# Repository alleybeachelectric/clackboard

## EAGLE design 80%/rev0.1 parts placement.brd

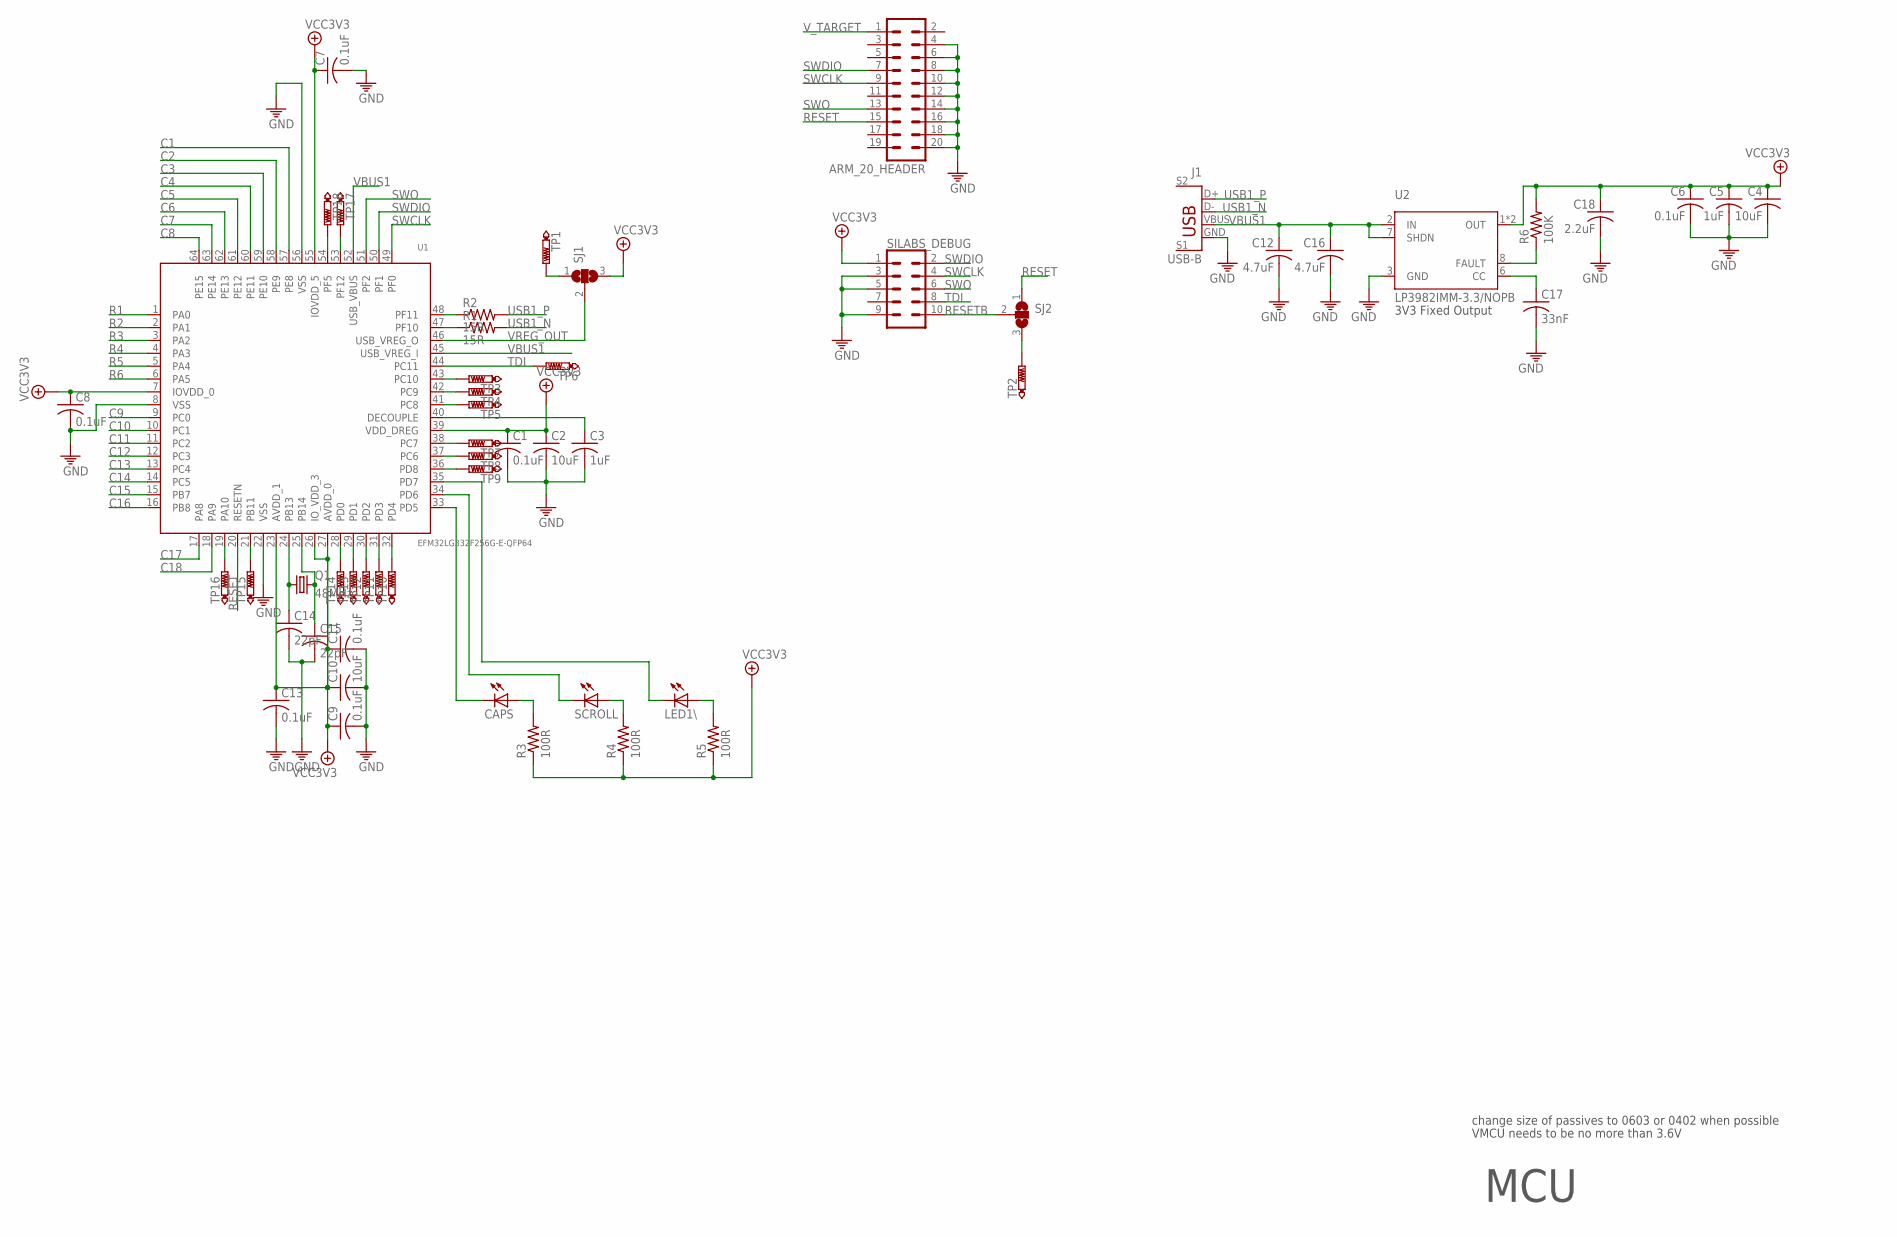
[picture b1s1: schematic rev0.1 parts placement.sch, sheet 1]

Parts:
ARM_20_HEADER: MA10-2
C1, C6, C7, C8, C9, C11, C13: 0.1uF; C0402
C2, C4, C10: 10uF; C0805
C3, C5: 1uF; C0402
C12, C16: 4.7uF; C0805
C14, C15: 22pF; C0402
C17: 33nF; C0402
C18: 2.2uF; C0805
CAPS: LEDCHIP-LED0805; CHIP-LED0805
J1: USB-B; USB-B-PTH
LED1\: LEDCHIP-LED0805; CHIP-LED0805
Q1: 48MHz; CTS406
R1, R2: 15R; R0402
R3, R4, R5: 100R; R0402
R6: 100K; R0402
SCROLL: LEDCHIP-LED0805; CHIP-LED0805
SILABS_DEBUG: CONN_05X2SHD_LOCK; 2X5-SHROUDED_LOCK
SJ1, SJ2: SJ2W; SJ_2
TP1, TP2: PTR1B2,54; B2,54
TP3, TP4, TP5, TP6, TP7, TP8, TP9, TP10, TP11, TP12, TP13, TP14, TP15, TP16, TP17, TP18: PTR1B1,27; B1,27
U1: EFM32LG332F256G-E-QFP64
U2: LP3982IMM-3.3/NOPB

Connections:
1_N: R1.1, U1.47 (PF10)
1_P: R2.1, U1.48 (PF11)
C1: U1.57 (PE8); also elsewhere on the board
C2: U1.58 (PE9); also elsewhere on the board
C3: U1.59 (PE10); also elsewhere on the board
C4: U1.60 (PE11); also elsewhere on the board
C5: U1.61 (PE12); also elsewhere on the board
C6: U1.62 (PE13); also elsewhere on the board
C7: U1.63 (PE14); also elsewhere on the board
C8: U1.64 (PE15); also elsewhere on the board
C9: U1.9 (PC0); also elsewhere on the board
C10: U1.10 (PC1); also elsewhere on the board
C11: U1.11 (PC2); also elsewhere on the board
C12: U1.12 (PC3); also elsewhere on the board
C13: U1.13 (PC4); also elsewhere on the board
C14: U1.14 (PC5); also elsewhere on the board
C15: U1.15 (PB7); also elsewhere on the board
C16: U1.16 (PB8); also elsewhere on the board
C17: U1.17 (PA8); also elsewhere on the board
C18: U1.18 (PA9); also elsewhere on the board
GND: ARM_20_HEADER.4, ARM_20_HEADER.6, ARM_20_HEADER.8, ARM_20_HEADER.10, ARM_20_HEADER.12, ARM_20_HEADER.14, ARM_20_HEADER.16, ARM_20_HEADER.18, ARM_20_HEADER.20, C1.2, C2.2, C3.2, C4.2, C5.2, C6.2, C7.2, C8.2, C9.2, C10.2, C11.2, C12.2, C13.2, C14.2, C15.2, C16.2, C17.2, C18.2, J1.GND, SILABS_DEBUG.3, SILABS_DEBUG.5, SILABS_DEBUG.9, U1.8 (VSS), U1.22 (VSS), U1.56 (VSS), U2.3 (GND)
unnamed: SJ1.1, TP1.TP
unnamed: C3.1, U1.40 (DECOUPLE)
unnamed: C15.1, Q1.3 (2), U1.25 (PB14)
unnamed: C14.1, Q1.1, U1.24 (PB13)
unnamed: SJ2.3, TP2.TP
unnamed: CAPS.A, R3.2
unnamed: R4.2, SCROLL.A
unnamed: LED1\.A, R5.2
unnamed: CAPS.C, U1.33 (PD5)
unnamed: SCROLL.C, U1.34 (PD6)
unnamed: LED1\.C, U1.35 (PD7)
unnamed: TP16.TP, U1.19 (PA10)
unnamed: C17.1, U2.6 (CC)
unnamed: R6.1, U2.8 (FAULT)
unnamed: TP15.TP, U1.21 (PB11)
unnamed: TP14.TP, U1.28 (PD0)
unnamed: TP13.TP, U1.29 (PD1)
unnamed: TP12.TP, U1.30 (PD2)
unnamed: TP11.TP, U1.31 (PD3)
unnamed: TP10.TP, U1.32 (PD4)
unnamed: TP9.TP, U1.36 (PD8)
unnamed: TP8.TP, U1.37 (PC6)
unnamed: TP7.TP, U1.38 (PC7)
unnamed: TP5.TP, U1.41 (PC8)
unnamed: TP4.TP, U1.42 (PC9)
unnamed: TP3.TP, U1.43 (PC10)
unnamed: TP17.TP, U1.53 (PF12)
unnamed: TP18.TP, U1.54 (PF5)
R1: U1.1 (PA0); also elsewhere on the board
R2: U1.2 (PA1); also elsewhere on the board
R3: U1.3 (PA2); also elsewhere on the board
R4: U1.4 (PA3); also elsewhere on the board
R5: U1.5 (PA4); also elsewhere on the board
R6: U1.6 (PA5); also elsewhere on the board
RESET: ARM_20_HEADER.15, SJ2.1, U1.20 (RESETN)
RESETB: SILABS_DEBUG.10, SJ2.2
SWCLK: ARM_20_HEADER.9, SILABS_DEBUG.4, U1.49 (PF0)
SWDIO: ARM_20_HEADER.7, SILABS_DEBUG.2, U1.50 (PF1)
SWO: ARM_20_HEADER.13, SILABS_DEBUG.6, U1.51 (PF2)
TDI: SILABS_DEBUG.8, TP6.TP, U1.44 (PC11)
USB1_N: J1.D-, R1.2
USB1_P: J1.D+, R2.2
VBUS1: C12.1, C16.1, J1.VBUS, U1.45 (USB_VREG_I), U1.52 (USB_VBUS), U2.2 (IN), U2.7 (SHDN)
VCC3V3: C1.1, C2.1, C4.1, C5.1, C6.1, C7.1, C8.1, C9.1, C10.1, C11.1, C13.1, C18.1, R3.1, R4.1, R5.1, R6.2, SILABS_DEBUG.1, SJ1.3, U1.7 (IOVDD_0), U1.23 (AVDD_1), U1.26 (IO_VDD_3), U1.27 (AVDD_0), U1.39 (VDD_DREG), U1.55 (IOVDD_5), U2.1 (OUT), U2.4 (OUT)
VREG_OUT: SJ1.2, U1.46 (USB_VREG_O)
V_TARGET: ARM_20_HEADER.1

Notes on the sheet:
change size of passives to 0603 or 0402 when possible
MCU
VMCU needs to be no more than 3.6V
3V3 Fixed Output

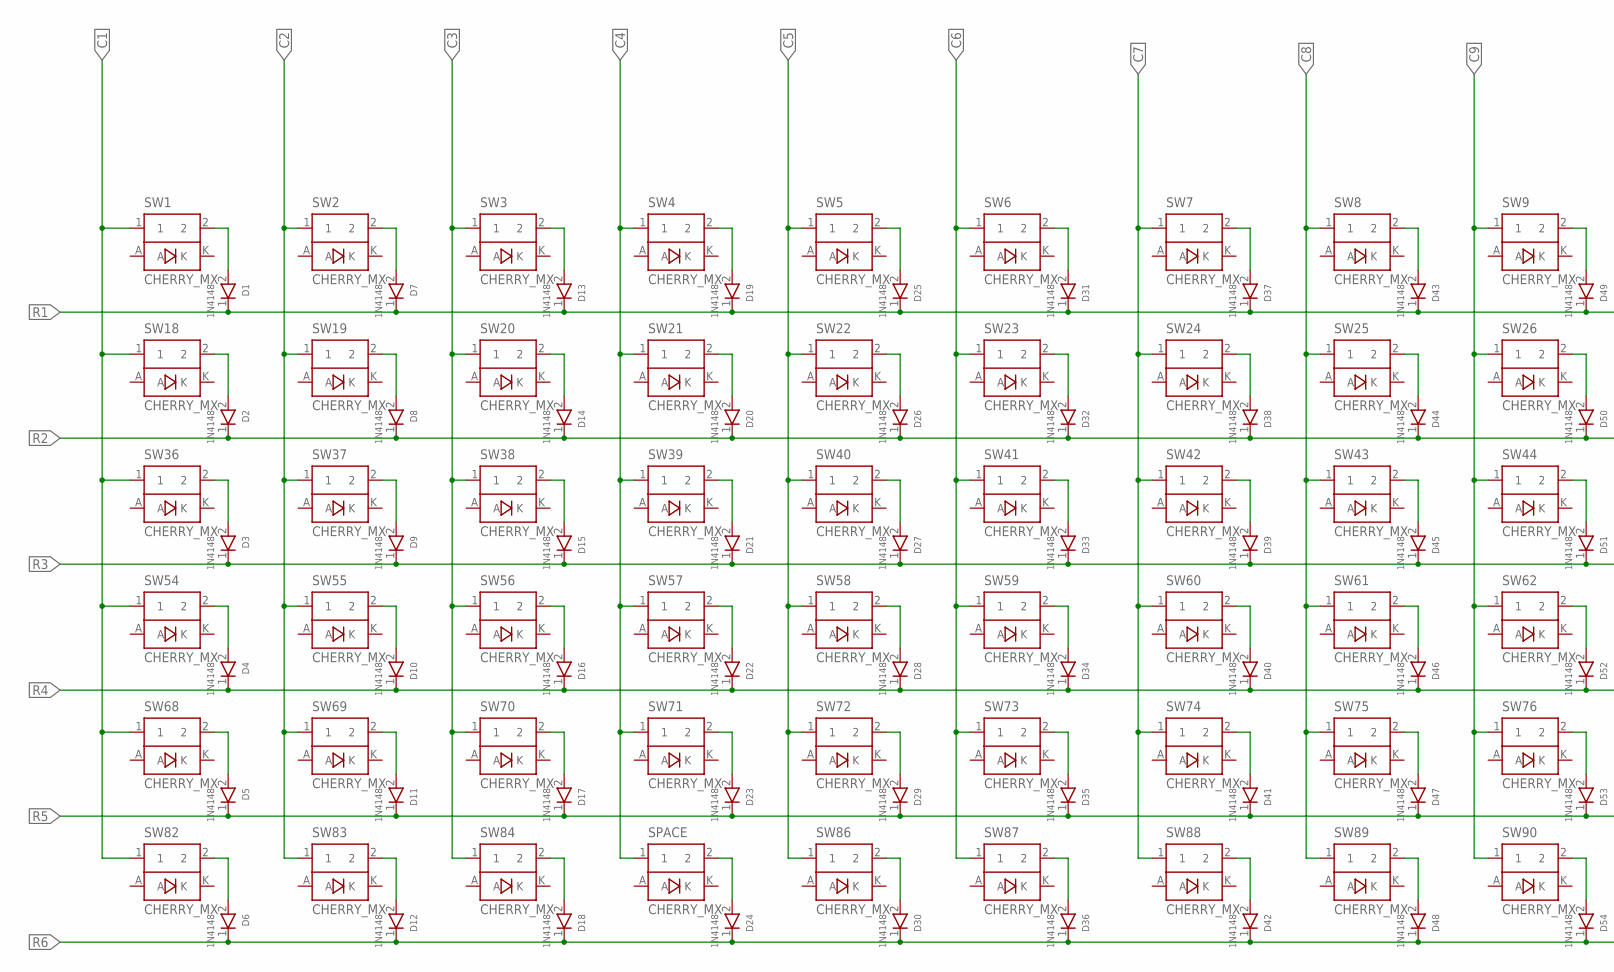
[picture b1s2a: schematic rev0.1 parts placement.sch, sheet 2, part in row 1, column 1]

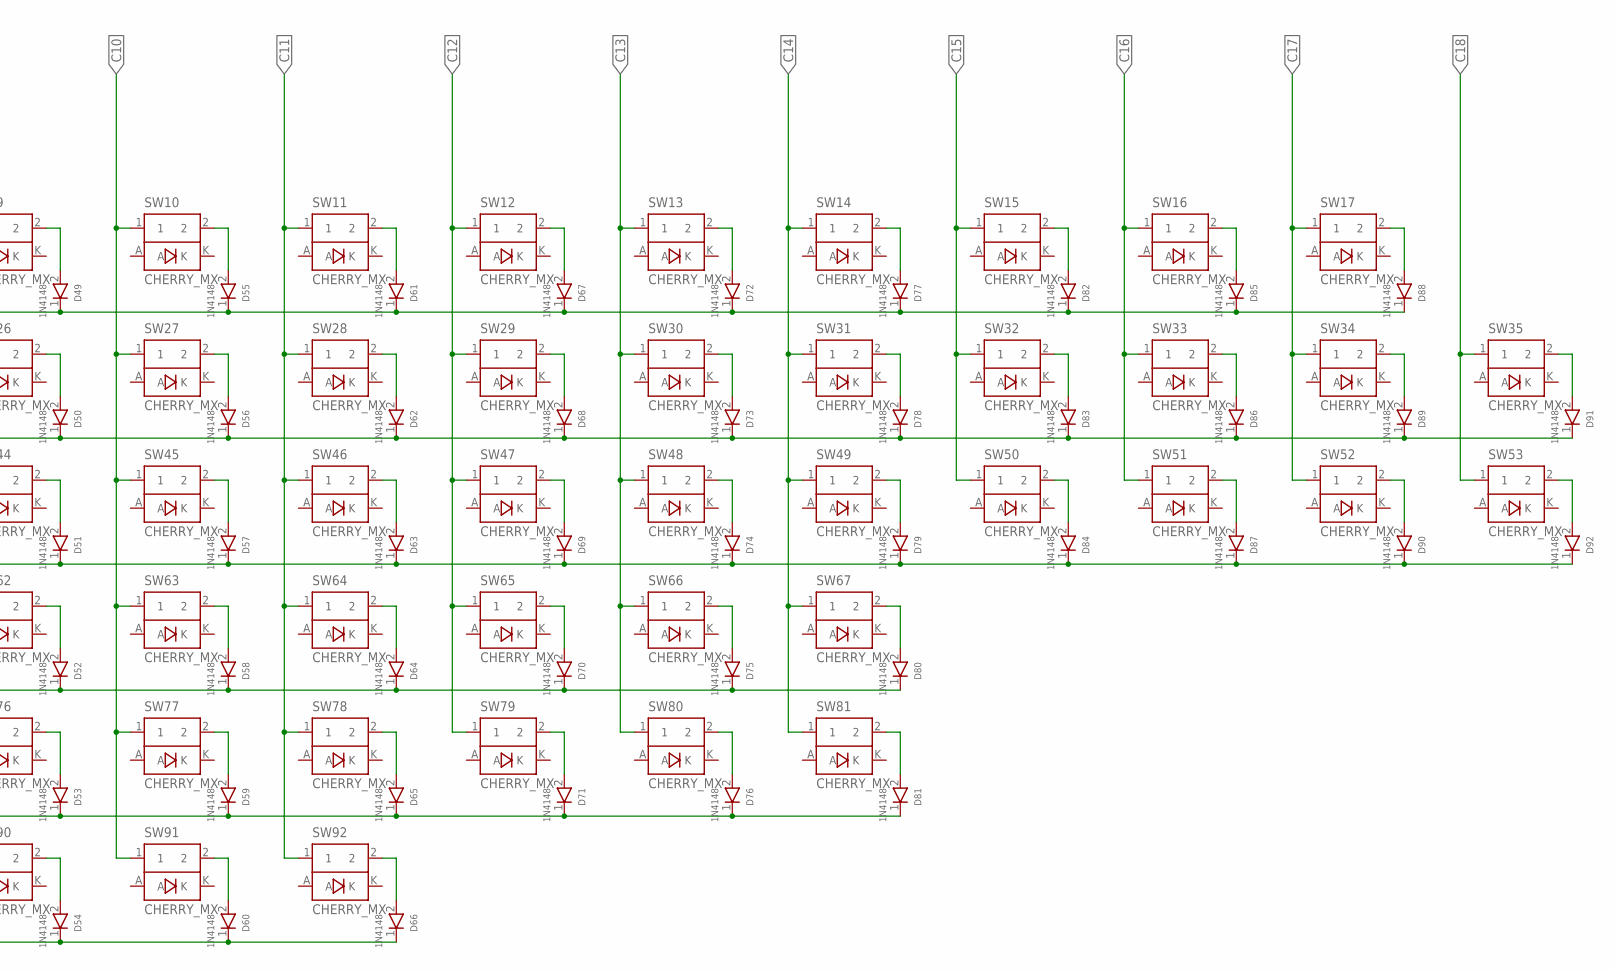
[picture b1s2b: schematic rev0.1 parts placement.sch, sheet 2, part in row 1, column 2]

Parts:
D1, D2, D3, D4, D5, D6, D7, D8, D9, D10, D11, D12, D13, D14, D15, D16, D17, D18, D19, D20, D21, D22, D23, D24, D25, D26, D27, D28, D29, D30, D31, D32, D33, D34, D35, D36, D37, D38, D39, D40, D41, D42, D43, D44, D45, D46, D47, D48, D49, D50, D51, D52, D53, D54, D55, D56, D57, D58, D59, D60, D61, D62, D63, D64, D65, D66, D67, D68, D69, D70, D71, D72, D73, D74, D75, D76, D77, D78, D79, D80, D81, D82, D83, D84, D85, D86, D87, D88, D89, D90, D91, D92: 1N4148; SOD323
SPACE: CHERRY_MX
SW1, SW2, SW3, SW4, SW5, SW6, SW7, SW8, SW9, SW10, SW11, SW12, SW13, SW14, SW15, SW16, SW17, SW18, SW19, SW20, SW21, SW22, SW23, SW24, SW25, SW26, SW27, SW28, SW29, SW30, SW31, SW32, SW33, SW34, SW35, SW36, SW37, SW38, SW39, SW40, SW41, SW42, SW43, SW44, SW45, SW46, SW47, SW48, SW49, SW50, SW51, SW52, SW53, SW54, SW55, SW56, SW57, SW58, SW59, SW60, SW61, SW62, SW63, SW64, SW65, SW66, SW67, SW68, SW69, SW70, SW71, SW72, SW73, SW74, SW75, SW76, SW77, SW78, SW79, SW80, SW81, SW82, SW83, SW84, SW86, SW87, SW88, SW89, SW90, SW91, SW92: CHERRY_MX

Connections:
C1: SW1.1, SW18.1, SW36.1, SW54.1, SW68.1, SW82.1; also elsewhere on the board
C2: SW2.1, SW19.1, SW37.1, SW55.1, SW69.1, SW83.1; also elsewhere on the board
C3: SW3.1, SW20.1, SW38.1, SW56.1, SW70.1, SW84.1; also elsewhere on the board
C4: SPACE.1, SW4.1, SW21.1, SW39.1, SW57.1, SW71.1; also elsewhere on the board
C5: SW5.1, SW22.1, SW40.1, SW58.1, SW72.1, SW86.1; also elsewhere on the board
C6: SW6.1, SW23.1, SW41.1, SW59.1, SW73.1, SW87.1; also elsewhere on the board
C7: SW7.1, SW24.1, SW42.1, SW60.1, SW74.1, SW88.1; also elsewhere on the board
C8: SW8.1, SW25.1, SW43.1, SW61.1, SW75.1, SW89.1; also elsewhere on the board
C9: SW9.1, SW26.1, SW44.1, SW62.1, SW76.1, SW90.1; also elsewhere on the board
C10: SW10.1, SW27.1, SW45.1, SW63.1, SW77.1, SW91.1; also elsewhere on the board
C11: SW11.1, SW28.1, SW46.1, SW64.1, SW78.1, SW92.1; also elsewhere on the board
C12: SW12.1, SW29.1, SW47.1, SW65.1, SW79.1; also elsewhere on the board
C13: SW13.1, SW30.1, SW48.1, SW66.1, SW80.1; also elsewhere on the board
C14: SW14.1, SW31.1, SW49.1, SW67.1, SW81.1; also elsewhere on the board
C15: SW15.1, SW32.1, SW50.1; also elsewhere on the board
C16: SW16.1, SW33.1, SW51.1; also elsewhere on the board
C17: SW17.1, SW34.1, SW52.1; also elsewhere on the board
C18: SW35.1, SW53.1; also elsewhere on the board
unnamed: D88.2, SW17.2
unnamed: D6.2, SW82.2
unnamed: D5.2, SW68.2
unnamed: D4.2, SW54.2
unnamed: D3.2, SW36.2
unnamed: D2.2, SW18.2
unnamed: D1.2, SW1.2
unnamed: D91.2, SW35.2
unnamed: D7.2, SW2.2
unnamed: D12.2, SW83.2
unnamed: D11.2, SW69.2
unnamed: D10.2, SW55.2
unnamed: D9.2, SW37.2
unnamed: D8.2, SW19.2
unnamed: D92.2, SW53.2
unnamed: D90.2, SW52.2
unnamed: D89.2, SW34.2
unnamed: D85.2, SW16.2
unnamed: D14.2, SW20.2
unnamed: D13.2, SW3.2
unnamed: D15.2, SW38.2
unnamed: D21.2, SW39.2
unnamed: D20.2, SW21.2
unnamed: D22.2, SW57.2
unnamed: D16.2, SW56.2
unnamed: D17.2, SW70.2
unnamed: D23.2, SW71.2
unnamed: D24.2, SPACE.2
unnamed: D18.2, SW84.2
unnamed: D19.2, SW4.2
unnamed: D25.2, SW5.2
unnamed: D31.2, SW6.2
unnamed: D26.2, SW22.2
unnamed: D32.2, SW23.2
unnamed: D33.2, SW41.2
unnamed: D27.2, SW40.2
unnamed: D28.2, SW58.2
unnamed: D34.2, SW59.2
unnamed: D35.2, SW73.2
unnamed: D29.2, SW72.2
unnamed: D30.2, SW86.2
unnamed: D36.2, SW87.2
unnamed: D86.2, SW33.2
unnamed: D87.2, SW51.2
unnamed: D84.2, SW50.2
unnamed: D83.2, SW32.2
unnamed: D82.2, SW15.2
unnamed: D77.2, SW14.2
unnamed: D78.2, SW31.2
unnamed: D79.2, SW49.2
unnamed: D80.2, SW67.2
unnamed: D81.2, SW81.2
unnamed: D76.2, SW80.2
unnamed: D75.2, SW66.2
unnamed: D70.2, SW65.2
unnamed: D71.2, SW79.2
unnamed: D69.2, SW47.2
unnamed: D74.2, SW48.2
unnamed: D73.2, SW30.2
unnamed: D68.2, SW29.2
unnamed: D67.2, SW12.2
unnamed: D72.2, SW13.2
unnamed: D61.2, SW11.2
unnamed: D55.2, SW10.2
unnamed: D56.2, SW27.2
unnamed: D62.2, SW28.2
unnamed: D63.2, SW46.2
unnamed: D57.2, SW45.2
unnamed: D58.2, SW63.2
unnamed: D64.2, SW64.2
unnamed: D65.2, SW78.2
unnamed: D59.2, SW77.2
unnamed: D60.2, SW91.2
unnamed: D66.2, SW92.2
unnamed: D48.2, SW89.2
unnamed: D54.2, SW90.2
unnamed: D47.2, SW75.2
unnamed: D53.2, SW76.2
unnamed: D52.2, SW62.2
unnamed: D46.2, SW61.2
unnamed: D45.2, SW43.2
unnamed: D51.2, SW44.2
unnamed: D50.2, SW26.2
unnamed: D44.2, SW25.2
unnamed: D43.2, SW8.2
unnamed: D49.2, SW9.2
unnamed: D37.2, SW7.2
unnamed: D38.2, SW24.2
unnamed: D39.2, SW42.2
unnamed: D40.2, SW60.2
unnamed: D41.2, SW74.2
unnamed: D42.2, SW88.2
R1: D1.1, D7.1, D13.1, D19.1, D25.1, D31.1, D37.1, D43.1, D49.1, D55.1, D61.1, D67.1, D72.1, D77.1, D82.1, D85.1, D88.1; also elsewhere on the board
R2: D2.1, D8.1, D14.1, D20.1, D26.1, D32.1, D38.1, D44.1, D50.1, D56.1, D62.1, D68.1, D73.1, D78.1, D83.1, D86.1, D89.1, D91.1; also elsewhere on the board
R3: D3.1, D9.1, D15.1, D21.1, D27.1, D33.1, D39.1, D45.1, D51.1, D57.1, D63.1, D69.1, D74.1, D79.1, D84.1, D87.1, D90.1, D92.1; also elsewhere on the board
R4: D4.1, D10.1, D16.1, D22.1, D28.1, D34.1, D40.1, D46.1, D52.1, D58.1, D64.1, D70.1, D75.1, D80.1; also elsewhere on the board
R5: D5.1, D11.1, D17.1, D23.1, D29.1, D35.1, D41.1, D47.1, D53.1, D59.1, D65.1, D71.1, D76.1, D81.1; also elsewhere on the board
R6: D6.1, D12.1, D18.1, D24.1, D30.1, D36.1, D42.1, D48.1, D54.1, D60.1, D66.1; also elsewhere on the board

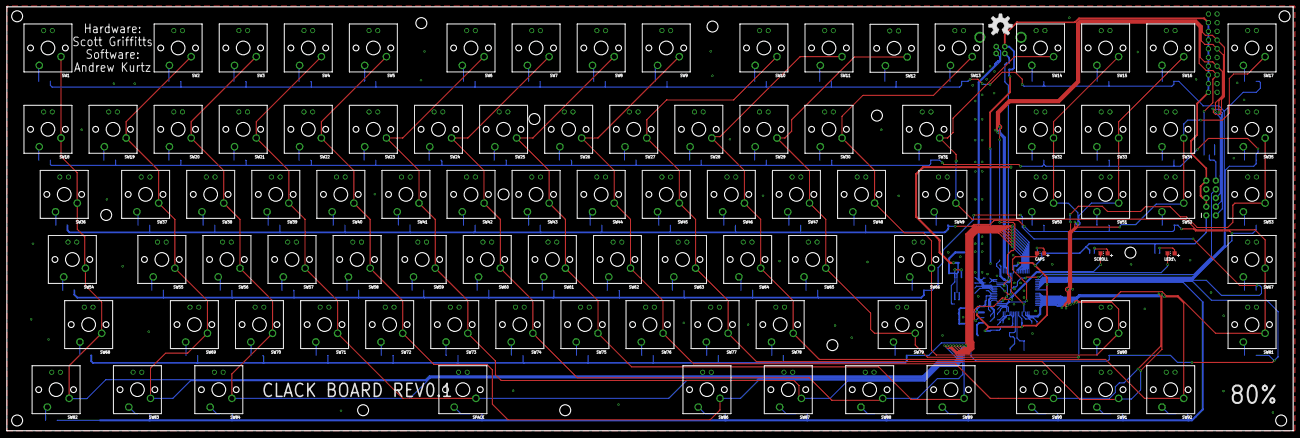
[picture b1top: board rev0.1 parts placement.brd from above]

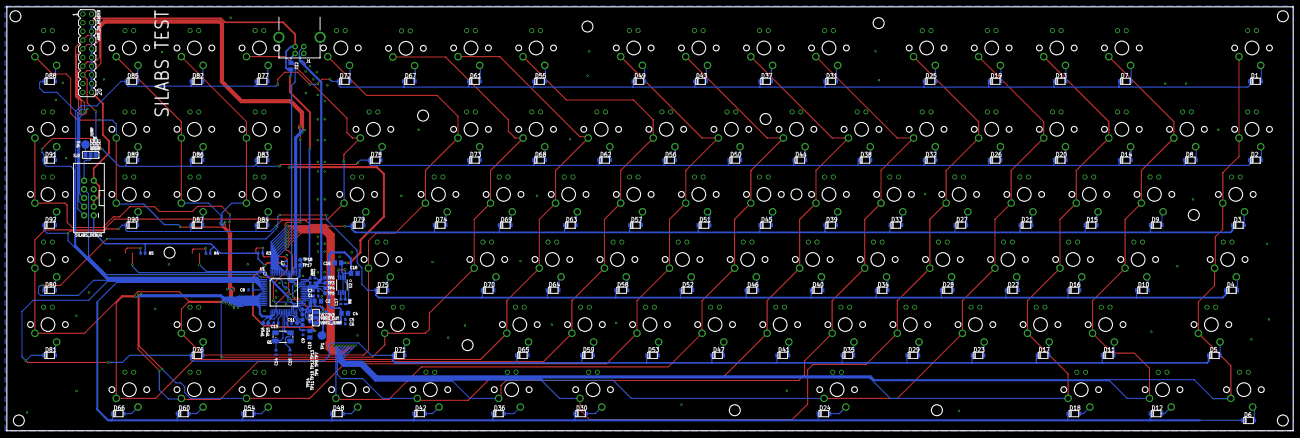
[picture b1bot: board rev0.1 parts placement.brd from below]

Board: 2 copper layers, 375.5 x 123.8 mm, 238 parts (142 on the bottom side), 158 nets.

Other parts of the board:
U$15: OSHW-LOGO-L

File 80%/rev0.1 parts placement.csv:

Qty,Value,Device,Package,Parts,Description,MF,MPN,OC_FARNELL,OC_NEWARK,PROD_ID,SF_ID,TP_SIGNAL_NAME,VALUE
1,,CONN_05X2SHD_LOCK,2X5-SHROUDED_LOCK,SILABS_DEBUG,Multi connection point. Often used as Generic Header-pin footprint for 0.1 inch spaced/style header connections,,,,,CONN-08671,PRT-08506,,
3,,LEDCHIP-LED0805,CHIP-LED0805,"CAPS, LED1\, SCROLL",LED,,,,,,,,
1,,MA10-2,MA10-2,ARM_20_HEADER,PIN HEADER,,,unknown,unknown,,,,
2,,SJ2W,SJ_2,"SJ1, SJ2",SMD solder JUMPER,,,,,,,,
7,0.1uF,C-USC0402,C0402,"C1, C6, C7, C8, C9, C11, C13","CAPACITOR, American symbol",,,,,,,,
1,100K,R-US_R0402,R0402,R6,"RESISTOR, American symbol",,,,,,,,
3,100R,R-US_R0402,R0402,"R3, R4, R5","RESISTOR, American symbol",,,,,,,,
3,10uF,C-USC0805,C0805,"C2, C4, C10","CAPACITOR, American symbol",,,,,,,,
2,15R,R-US_R0402,R0402,"R1, R2","RESISTOR, American symbol",,,,,,,,
92,1N4148,1N4148,SOD323,"D1, D2, D3, D4, D5, D6, D7, D8, D9, D10, D11, D12, D13, D14, D15, D16, D17, D18, D19, D20, D21, D22, D23, D24, D25, D26, D27, D28, D29, D30, D31, D32, D33, D34, D35, D36, D37, D38, D39, D40, D41, D42, D43, D44, D45, D46, D47, D48, D49, D50, D51, D52, D53, D54, D55, D56, D57, D58, D59, D60, D61, D62, D63, D64, D65, D66, D67, D68, D69, D70, D71, D72, D73, D74, D75, D76, D77, D78, D79, D80, D81, D82, D83, D84, D85, D86, D87, D88, D89, D90, D91, D92",,,,,,,,,
2,1uF,C-USC0402,C0402,"C3, C5","CAPACITOR, American symbol",,,,,,,,
1,2.2uF,C-USC0805,C0805,C18,"CAPACITOR, American symbol",,,,,,,,
2,22pF,C-USC0402,C0402,"C14, C15","CAPACITOR, American symbol",,,,,,,,
1,33nF,C-USC0402,C0402,C17,"CAPACITOR, American symbol",,,,,,,,
2,4.7uF,C-USC0805,C0805,"C12, C16","CAPACITOR, American symbol",,,,,,,,
1,48MHz,CRYSTALCTS406,CTS406,Q1,CRYSTAL,,,unknown,unknown,,,,
92,CHERRY_MX,CHERRY_MX,CHERRY_MX,"SPACE, SW1, SW2, SW3, SW4, SW5, SW6, SW7, SW8, SW9, SW10, SW11, SW12, SW13, SW14, SW15, SW16, SW17, SW18, SW19, SW20, SW21, SW22, SW23, SW24, SW25, SW26, SW27, SW28, SW29, SW30, SW31, SW32, SW33, SW34, SW35, SW36, SW37, SW38, SW39, SW40, SW41, SW42, SW43, SW44, SW45, SW46, SW47, SW48, SW49, SW50, SW51, SW52, SW53, SW54, SW55, SW56, SW57, SW58, SW59, SW60, SW61, SW62, SW63, SW64, SW65, SW66, SW67, SW68, SW69, SW70, SW71, SW72, SW73, SW74, SW75, SW76, SW77, SW78, SW79, SW80, SW81, SW82, SW83, SW84, SW86, SW87, SW88, SW89, SW90, SW91, SW92",,,,,,,,,
1,EFM32LG332F256G-E-QFP64,EFM32LG332F256G-E-QFP64,EFM32LG332F256G-E-QFP64,U1,,,,,,,,,
1,LP3982IMM-3.3/NOPB,LP3982IMM-3.3/NOPB,LP3982IMM-3.3/NOPB,U2,,,,,,,,,
16,"PTR1B1,27","PTR1B1,27","B1,27","TP3, TP4, TP5, TP6, TP7, TP8, TP9, TP10, TP11, TP12, TP13, TP14, TP15, TP16, TP17, TP18",TEST PIN,,,,,,,,
2,"PTR1B2,54","PTR1B2,54","B2,54","TP1, TP2",TEST PIN,,,,,,,,
1,USB-B,USBPTH,USB-B-PTH,J1,USB Connectors,,,,,CONN-08278,,,USB-B

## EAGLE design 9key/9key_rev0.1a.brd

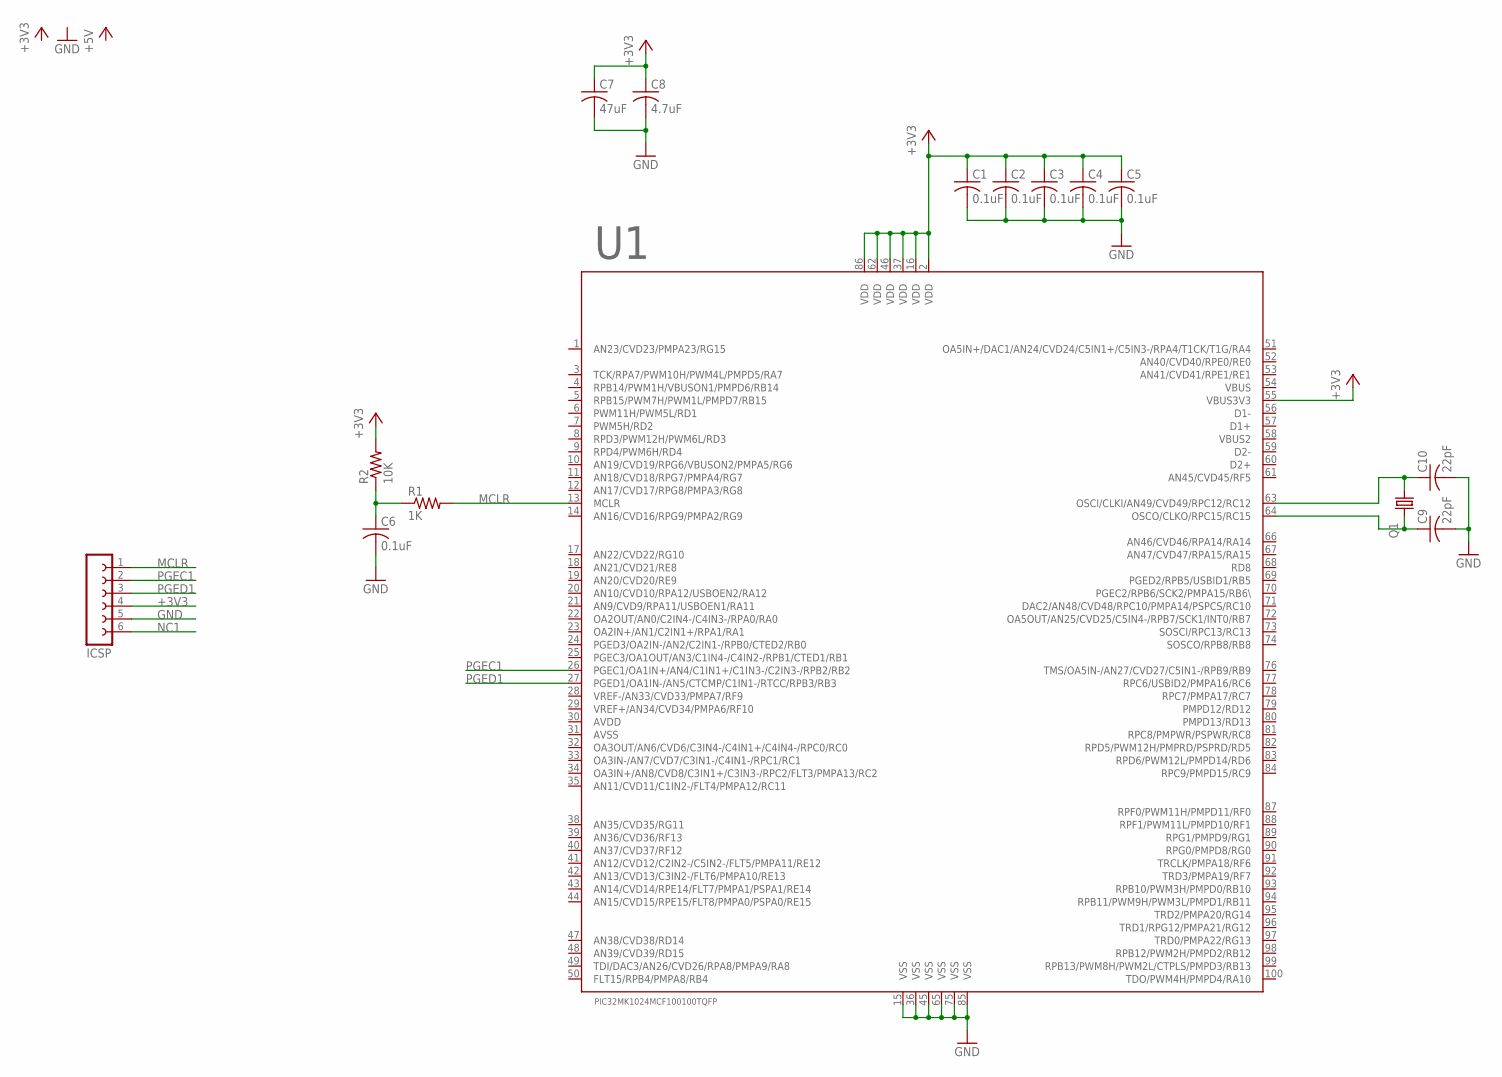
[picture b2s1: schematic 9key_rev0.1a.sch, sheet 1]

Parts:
C1, C2, C3, C4, C5, C6: 0.1uF; C0805
C7: 47uF; C0805
C8: 4.7uF; C0805
C9, C10: 22pF; C0603
ICSP: FE06-1; FE06
Q1: KX-7; 3.2X2.5_KX-7
R1: 1K; R0805
R2: 10K; R0805
U1: PIC32MK1024MCF100100TQFP; PIC32MK1024MCF100

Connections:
+3V3: C1.1, C2.1, C3.1, C4.1, C5.1, C7.1, C8.1, ICSP.4, R2.2, U1.2 (VDD), U1.16 (VDD), U1.37 (VDD), U1.46 (VDD), U1.55 (VBUS3V3), U1.62 (VDD), U1.86 (VDD)
GND: C1.2, C2.2, C3.2, C4.2, C5.2, C6.2, C7.2, C8.2, C9.2, C10.2, ICSP.5, U1.15 (VSS), U1.36 (VSS), U1.45 (VSS), U1.65 (VSS), U1.75 (VSS), U1.85 (VSS)
MCLR: ICSP.1, R1.2, U1.13 (MCLR)
unnamed: C6.1, R1.1, R2.1
NC1: ICSP.6
OSCIN: C10.1, Q1.1, U1.63 (OSCI/CLKI/AN49/CVD49/RPC12/RC12)
OSCOUT: C9.1, Q1.3 (2), U1.64 (OSCO/CLKO/RPC15/RC15)
PGEC1: ICSP.2, U1.26 (PGEC1/OA1IN+/AN4/C1IN1+/C1IN3-/C2IN3-/R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)
PGED1: ICSP.3, U1.27 (PGED1/OA1IN-/AN5/CTCMP/C1IN1-/RTCC/RPB3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)

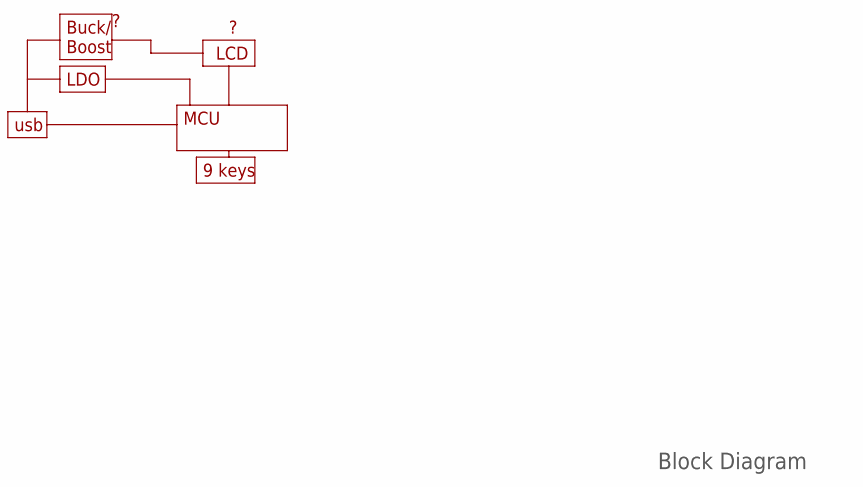
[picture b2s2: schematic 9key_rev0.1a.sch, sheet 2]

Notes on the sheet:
Block Diagram
usb
MCU
9 keys
LDO
LCD
Buck/ Boost

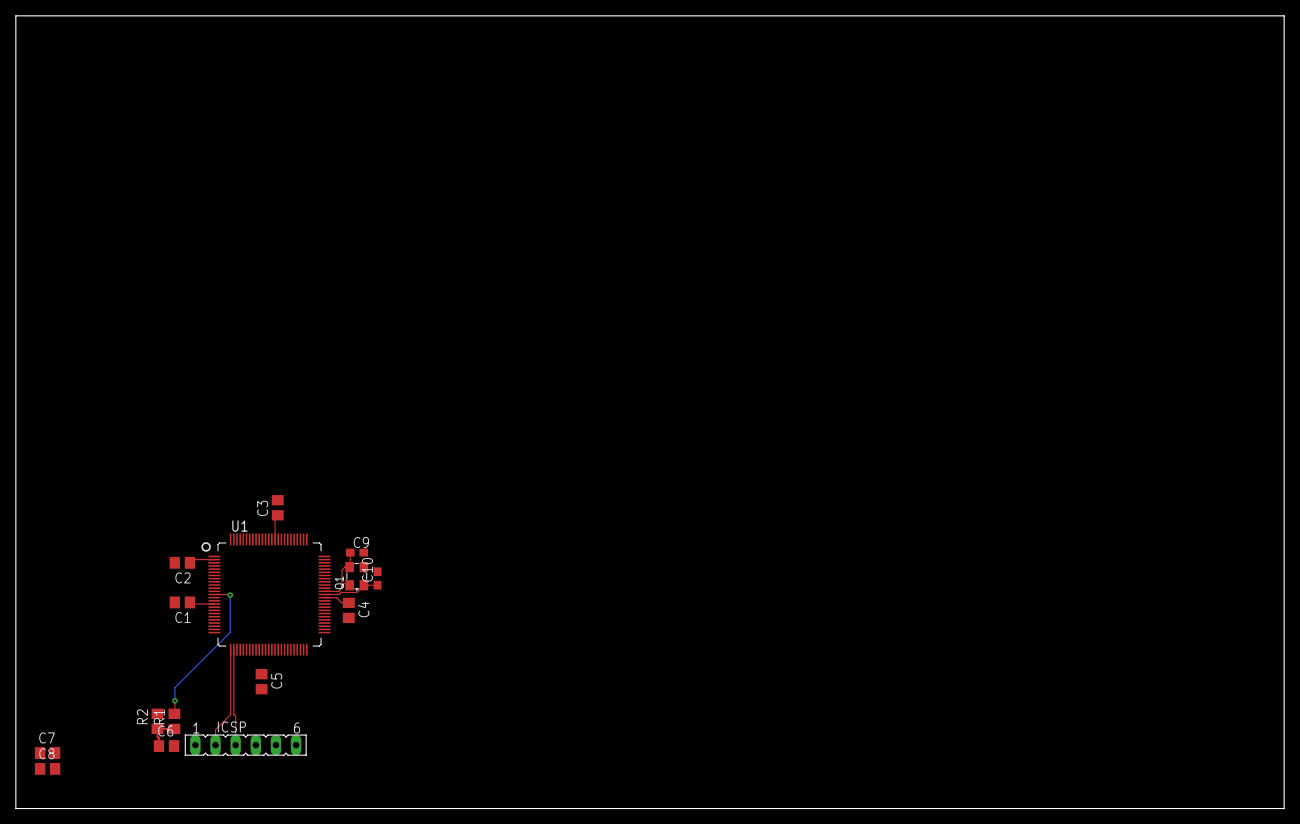
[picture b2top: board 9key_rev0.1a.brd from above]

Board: 2 copper layers, 160.0 x 100.0 mm, 15 parts (0 on the bottom side), 8 nets.

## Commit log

2017-08-18 initial commit
    initial commit
2017-08-18 init
2017-08-18 added block diagram for 9 key
2017-08-18 created pic part
    addd parts library
2017-08-30 added keys!!!
2017-09-27 laying matrix done
    laying matrix done
2017-10-06 did some reorienting
2017-10-26 add lib
2017-10-26 shit
2017-11-16 changed MCU
    changed MCU to a silicon labs MCU. EFM32. need to design power management and we will be groovy!
2017-11-20 cleaned up a little
    added power routing
2017-12-15 rev0.1 routed
2018-02-06 80 update
    updated the 80% with a new diode.
2018-02-07 added gerbers
2018-03-01 updated lib and added gerbers.
2018-03-06 added gerbers, cam, and library
2018-03-06 cleanup
2018-03-06 eesh
2018-03-15 fix?
2018-03-15 library fix?
2018-03-15 closer to clean

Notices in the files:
parts and their libraries:
SparkFun-Connectors: Licensing: Creative Commons ShareAlike 4.0 International - https://creativecommons.org/licenses/by-sa/4.0
crystal-geyer_V1_0: Copyright: Geyer-Electronic
